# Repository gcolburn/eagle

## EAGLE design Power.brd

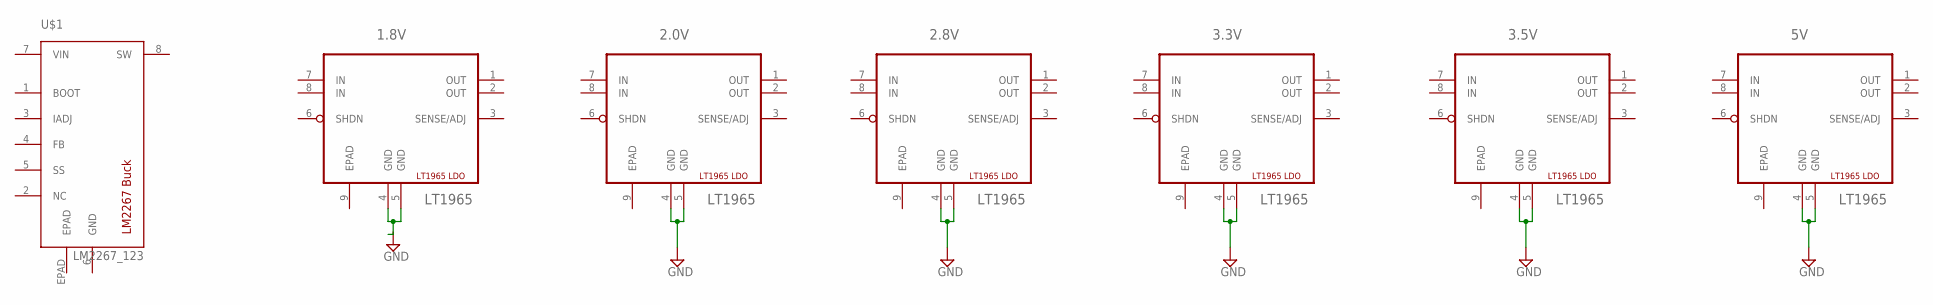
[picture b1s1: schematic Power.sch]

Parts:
1.8V, 2.0V, 2.8V, 3.3V, 3.5V, 5V: LT1965; DFN3X3_8LEAD
U$1: LM2267_123; DDA0008B

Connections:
BOOT: U$1.1 (BOOT)
EPAD: 1.8V.9 (EPAD), 2.0V.9 (EPAD), 2.8V.9 (EPAD), 3.3V.9 (EPAD), 3.5V.9 (EPAD), 5V.9 (EPAD), U$1.EPAD
GND: 2.0V.4 (GND), 2.0V.5 (GND), 2.8V.4 (GND), 2.8V.5 (GND), 3.3V.4 (GND), 3.3V.5 (GND), 3.5V.4 (GND), 3.5V.5 (GND), 5V.4 (GND), 5V.5 (GND), U$1.6 (GND)
IN: 1.8V.7 (IN), 1.8V.8 (IN), 2.0V.7 (IN), 2.0V.8 (IN), 2.8V.7 (IN), 2.8V.8 (IN), 3.3V.7 (IN), 3.3V.8 (IN), 3.5V.7 (IN), 3.5V.8 (IN), 5V.7 (IN), 5V.8 (IN)
unnamed: 1.8V.4 (GND), 1.8V.5 (GND)
OUT: 1.8V.1 (OUT), 1.8V.2 (OUT), 2.0V.1 (OUT), 2.0V.2 (OUT), 2.8V.1 (OUT), 2.8V.2 (OUT), 3.3V.1 (OUT), 3.3V.2 (OUT), 3.5V.1 (OUT), 3.5V.2 (OUT), 5V.1 (OUT), 5V.2 (OUT)
SW: U$1.8 (SW)
VIN: U$1.7 (VIN)

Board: 2 copper layers, 7 parts (0 on the bottom side), 5 nets, no tracks yet.

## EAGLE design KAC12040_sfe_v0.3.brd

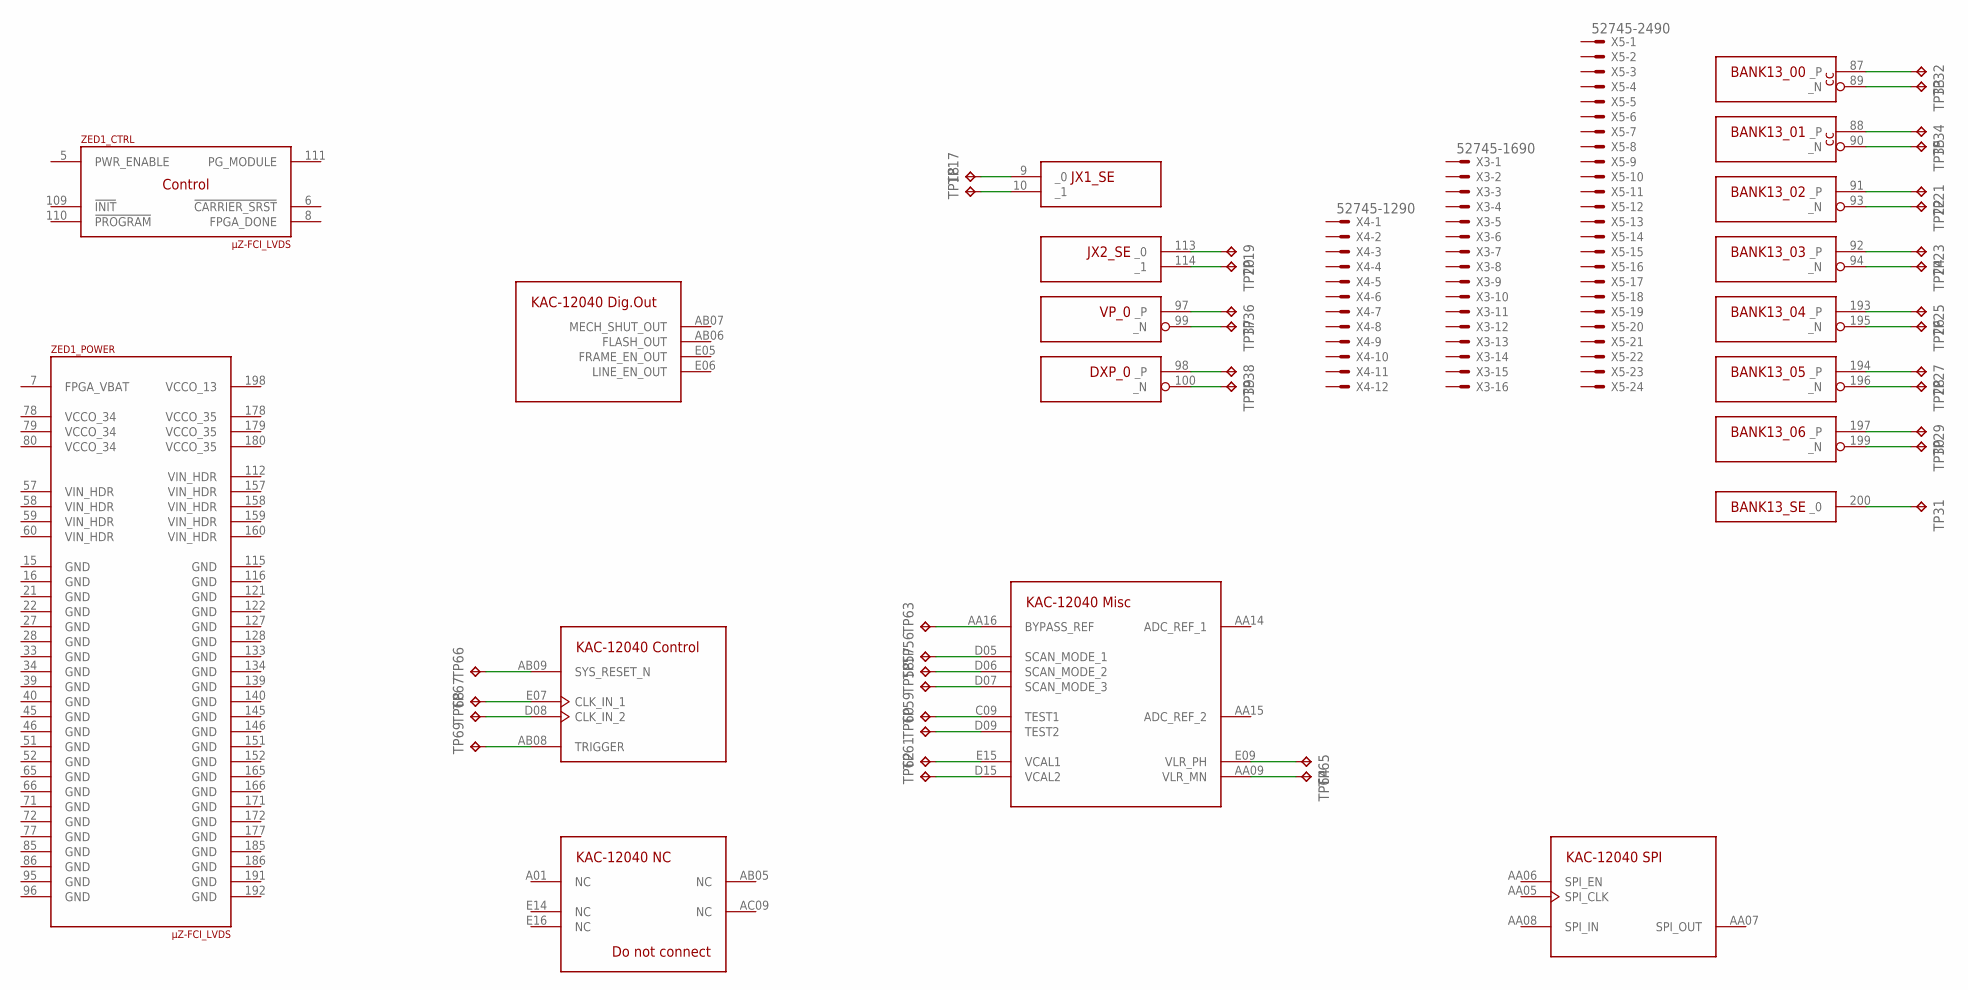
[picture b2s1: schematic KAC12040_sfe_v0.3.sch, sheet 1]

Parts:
TP17, TP18, TP19, TP20, TP31: TPPAD1-13; P1-13
TP21, TP22, TP23, TP24, TP25, TP26, TP27, TP28, TP29, TP30: TPTP08SQ; TP08SQ
TP32, TP33, TP34, TP35: TPTP18SQ; TP18SQ
TP36, TP37, TP38, TP39: TPPAD1-13Y; P1-13Y
TP56, TP57, TP58, TP59, TP60, TP61, TP62, TP63, TP64, TP65: TPTP15SQ; TP15SQ
TP66, TP67, TP68, TP69: TPTP15R; TP15R
U$1: KAC-12040-RB501T4
X3: 52745-1690
X4: 52745-1290
X5: 52745-2490
ZED1: µZ-FCI_LVDS; µZ

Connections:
FPGA_VBAT: ZED1.7 (FPGA_VBAT)
GND: ZED1.15 (GND), ZED1.16 (GND), ZED1.21 (GND), ZED1.22 (GND), ZED1.27 (GND), ZED1.28 (GND), ZED1.33 (GND), ZED1.34 (GND), ZED1.39 (GND), ZED1.40 (GND), ZED1.45 (GND), ZED1.46 (GND), ZED1.51 (GND), ZED1.52 (GND), ZED1.65 (GND), ZED1.66 (GND), ZED1.71 (GND), ZED1.72 (GND), ZED1.77 (GND), ZED1.85 (GND), ZED1.86 (GND), ZED1.95 (GND), ZED1.96 (GND), ZED1.115 (GND), ZED1.116 (GND), ZED1.121 (GND), ZED1.122 (GND), ZED1.127 (GND), ZED1.128 (GND), ZED1.133 (GND), ZED1.134 (GND), ZED1.139 (GND), ZED1.140 (GND), ZED1.145 (GND), ZED1.146 (GND), ZED1.151 (GND), ZED1.152 (GND), ZED1.165 (GND), ZED1.166 (GND), ZED1.171 (GND), ZED1.172 (GND), ZED1.177 (GND), ZED1.185 (GND), ZED1.186 (GND), ZED1.191 (GND), ZED1.192 (GND); also elsewhere on the board
unnamed: TP62.TP, U$1.D15 (VCAL2)
unnamed: TP61.TP, U$1.E15 (VCAL1)
unnamed: TP60.TP, U$1.D09 (TEST2)
unnamed: TP59.TP, U$1.C09 (TEST1)
unnamed: TP19.TP, ZED1.113 (_0)
unnamed: TP20.TP, ZED1.114 (_1)
unnamed: TP17.TP, ZED1.9 (_0)
unnamed: TP18.TP, ZED1.10 (_1)
unnamed: TP21.TP, ZED1.91 (_P)
unnamed: TP22.TP, ZED1.93 (_N)
unnamed: TP23.TP, ZED1.92 (_P)
unnamed: TP24.TP, ZED1.94 (_N)
unnamed: TP25.TP, ZED1.193 (_P)
unnamed: TP26.TP, ZED1.195 (_N)
unnamed: TP27.TP, ZED1.194 (_P)
unnamed: TP28.TP, ZED1.196 (_N)
unnamed: TP29.TP, ZED1.197 (_P)
unnamed: TP30.TP, ZED1.199 (_N)
unnamed: TP31.TP, ZED1.200 (_0)
unnamed: TP32.TP, ZED1.87 (_P)
unnamed: TP33.TP, ZED1.89 (_N)
unnamed: TP34.TP, ZED1.88 (_P)
unnamed: TP35.TP, ZED1.90 (_N)
unnamed: TP36.TP, ZED1.97 (_P)
unnamed: TP37.TP, ZED1.99 (_N)
unnamed: TP38.TP, ZED1.98 (_P)
unnamed: TP39.TP, ZED1.100 (_N)
unnamed: TP58.TP, U$1.D07 (SCAN_MODE_3)
unnamed: TP57.TP, U$1.D06 (SCAN_MODE_2)
unnamed: TP56.TP, U$1.D05 (SCAN_MODE_1)
unnamed: TP63.TP, U$1.AA16 (BYPASS_REF)
unnamed: TP65.TP, U$1.E09 (VLR_PH)
unnamed: TP64.TP, U$1.AA09 (VLR_MN)
unnamed: TP66.TP, U$1.AB09 (SYS_RESET_N)
unnamed: TP67.TP, U$1.E07 (CLK_IN_1)
unnamed: TP68.TP, U$1.D08 (CLK_IN_2)
unnamed: TP69.TP, U$1.AB08 (TRIGGER)
VCCO_13: ZED1.198 (VCCO_13)
VCCO_34: ZED1.78 (VCCO_34), ZED1.79 (VCCO_34), ZED1.80 (VCCO_34)
VCCO_35: ZED1.178 (VCCO_35), ZED1.179 (VCCO_35), ZED1.180 (VCCO_35)
VDDO: U$1.AB15 (VDDO)
VDD_PLL: U$1.E08 (VDD_PLL)
VIN_HDR: ZED1.57 (VIN_HDR), ZED1.58 (VIN_HDR), ZED1.59 (VIN_HDR), ZED1.60 (VIN_HDR), ZED1.112 (VIN_HDR), ZED1.157 (VIN_HDR), ZED1.158 (VIN_HDR), ZED1.159 (VIN_HDR), ZED1.160 (VIN_HDR)

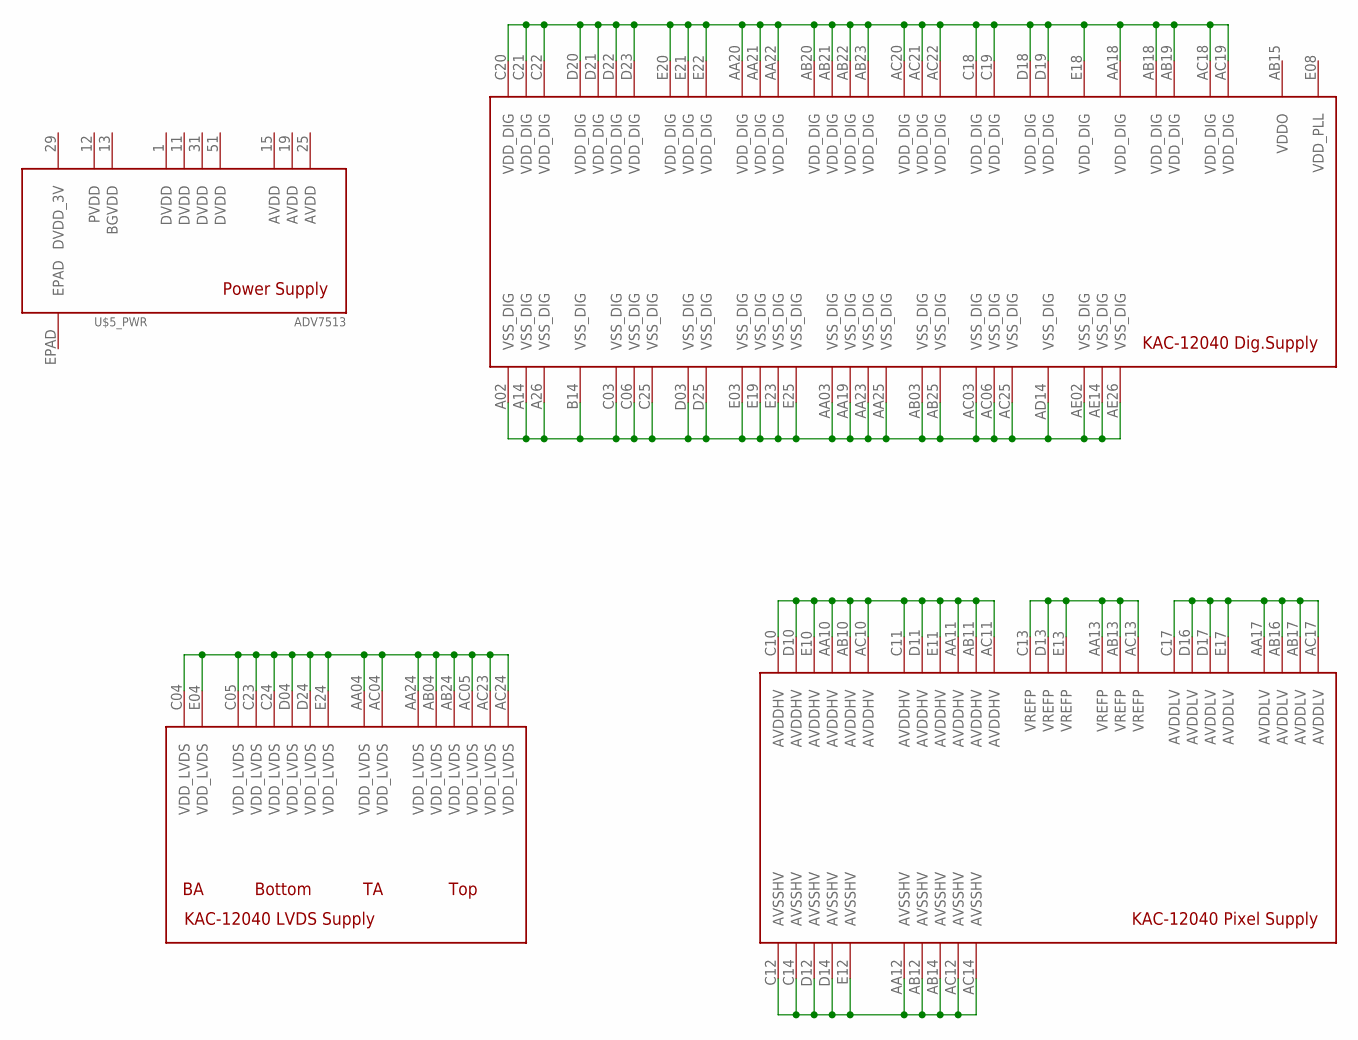
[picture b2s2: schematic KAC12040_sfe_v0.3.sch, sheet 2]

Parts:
U$1: KAC-12040-RB501T4
U$5: ADV7513; LQFP-ST-64-2

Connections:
AVDD: U$5.15 (AVDD), U$5.19 (AVDD), U$5.25 (AVDD)
AVDD_HV: U$1.AA10 (AVDDHV), U$1.AA11 (AVDDHV), U$1.AB10 (AVDDHV), U$1.AB11 (AVDDHV), U$1.AC10 (AVDDHV), U$1.AC11 (AVDDHV), U$1.C10 (AVDDHV), U$1.C11 (AVDDHV), U$1.D10 (AVDDHV), U$1.D11 (AVDDHV), U$1.E10 (AVDDHV), U$1.E11 (AVDDHV)
AVDD_LV: U$1.AA17 (AVDDLV), U$1.AB16 (AVDDLV), U$1.AB17 (AVDDLV), U$1.AC17 (AVDDLV), U$1.C17 (AVDDLV), U$1.D16 (AVDDLV), U$1.D17 (AVDDLV), U$1.E17 (AVDDLV)
AVSS_HV: U$1.AA12 (AVSSHV), U$1.AB12 (AVSSHV), U$1.AB14 (AVSSHV), U$1.AC12 (AVSSHV), U$1.AC14 (AVSSHV), U$1.C12 (AVSSHV), U$1.C14 (AVSSHV), U$1.D12 (AVSSHV), U$1.D14 (AVSSHV), U$1.E12 (AVSSHV)
BGVDD: U$5.13 (BGVDD)
DVDD: U$5.1 (DVDD), U$5.11 (DVDD), U$5.31 (DVDD), U$5.51 (DVDD)
DVDD_3V: U$5.29 (DVDD_3V)
EPAD: U$5.EPAD; also elsewhere on the board
PVDD: U$5.12 (PVDD)
VDDO: U$1.AB15 (VDDO)
VDD_DIG: U$1.AA18 (VDD_DIG), U$1.AA20 (VDD_DIG), U$1.AA21 (VDD_DIG), U$1.AA22 (VDD_DIG), U$1.AB18 (VDD_DIG), U$1.AB19 (VDD_DIG), U$1.AB20 (VDD_DIG), U$1.AB21 (VDD_DIG), U$1.AB22 (VDD_DIG), U$1.AB23 (VDD_DIG), U$1.AC18 (VDD_DIG), U$1.AC19 (VDD_DIG), U$1.AC20 (VDD_DIG), U$1.AC21 (VDD_DIG), U$1.AC22 (VDD_DIG), U$1.C18 (VDD_DIG), U$1.C19 (VDD_DIG), U$1.C20 (VDD_DIG), U$1.C21 (VDD_DIG), U$1.C22 (VDD_DIG), U$1.D18 (VDD_DIG), U$1.D19 (VDD_DIG), U$1.D20 (VDD_DIG), U$1.D21 (VDD_DIG), U$1.D22 (VDD_DIG), U$1.D23 (VDD_DIG), U$1.E18 (VDD_DIG), U$1.E20 (VDD_DIG), U$1.E21 (VDD_DIG), U$1.E22 (VDD_DIG)
VDD_LVDS: U$1.AA04 (VDD_LVDS), U$1.AA24 (VDD_LVDS), U$1.AB04 (VDD_LVDS), U$1.AB24 (VDD_LVDS), U$1.AC04 (VDD_LVDS), U$1.AC05 (VDD_LVDS), U$1.AC23 (VDD_LVDS), U$1.AC24 (VDD_LVDS), U$1.C04 (VDD_LVDS), U$1.C05 (VDD_LVDS), U$1.C23 (VDD_LVDS), U$1.C24 (VDD_LVDS), U$1.D04 (VDD_LVDS), U$1.D24 (VDD_LVDS), U$1.E04 (VDD_LVDS), U$1.E24 (VDD_LVDS)
VDD_PLL: U$1.E08 (VDD_PLL)
VREFP: U$1.AA13 (VREFP), U$1.AB13 (VREFP), U$1.AC13 (VREFP), U$1.C13 (VREFP), U$1.D13 (VREFP), U$1.E13 (VREFP)
VSS_DIG: U$1.A02 (VSS_DIG), U$1.A14 (VSS_DIG), U$1.A26 (VSS_DIG), U$1.AA03 (VSS_DIG), U$1.AA19 (VSS_DIG), U$1.AA23 (VSS_DIG), U$1.AA25 (VSS_DIG), U$1.AB03 (VSS_DIG), U$1.AB25 (VSS_DIG), U$1.AC03 (VSS_DIG), U$1.AC06 (VSS_DIG), U$1.AC25 (VSS_DIG), U$1.AD14 (VSS_DIG), U$1.AE02 (VSS_DIG), U$1.AE14 (VSS_DIG), U$1.AE26 (VSS_DIG), U$1.B14 (VSS_DIG), U$1.C03 (VSS_DIG), U$1.C06 (VSS_DIG), U$1.C25 (VSS_DIG), U$1.D03 (VSS_DIG), U$1.D25 (VSS_DIG), U$1.E03 (VSS_DIG), U$1.E19 (VSS_DIG), U$1.E23 (VSS_DIG), U$1.E25 (VSS_DIG)

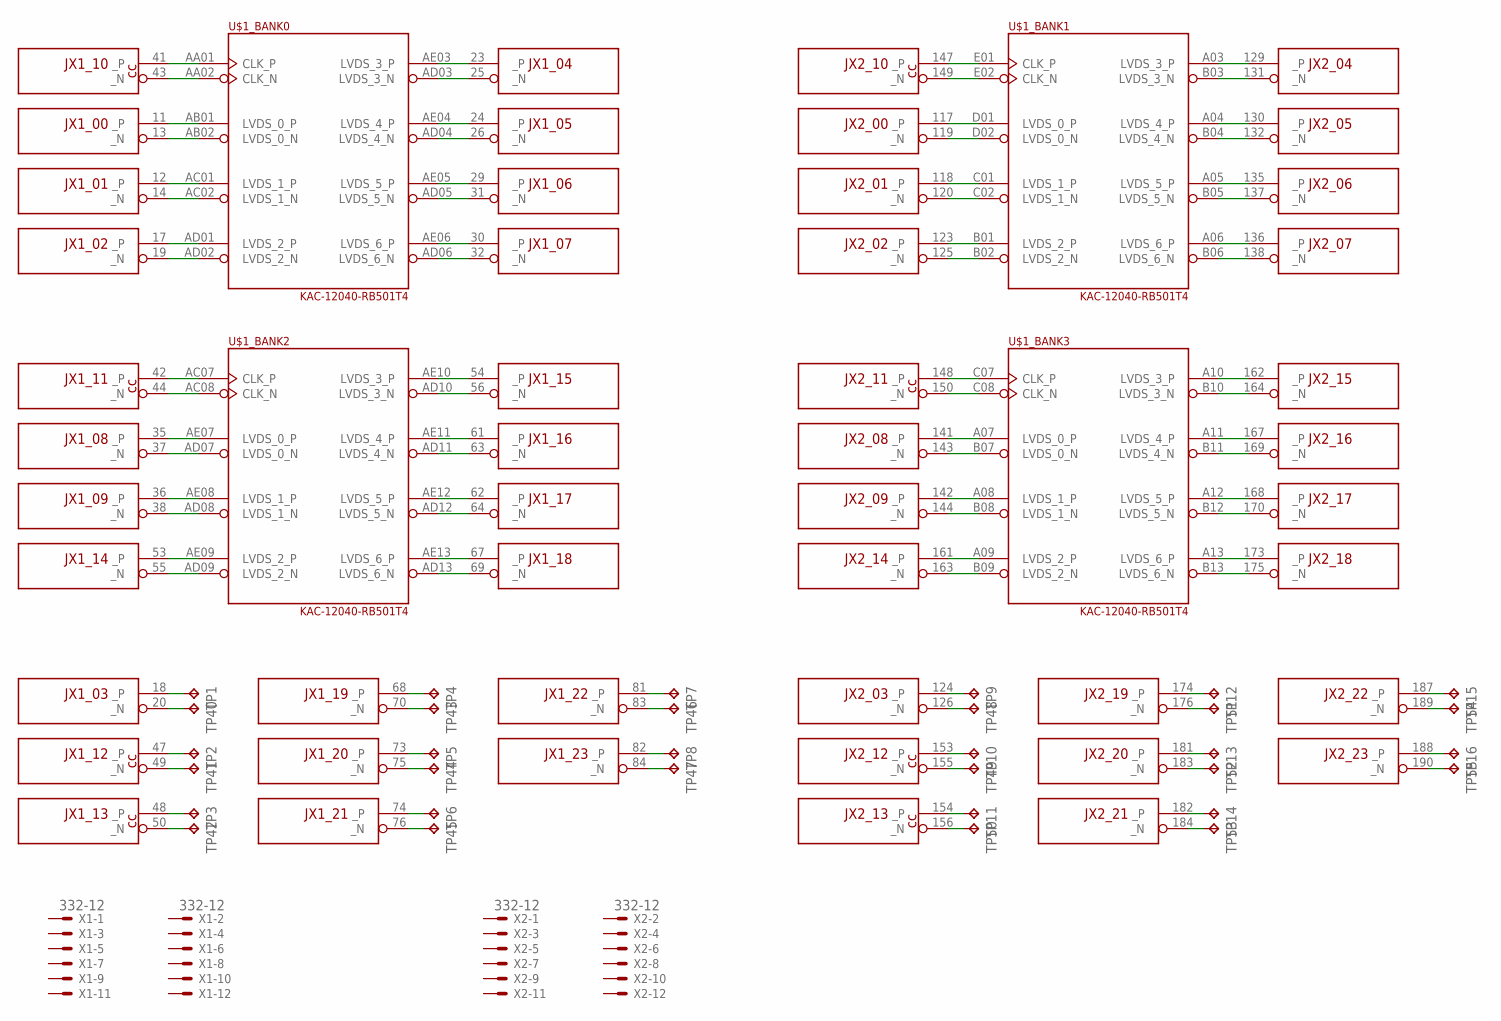
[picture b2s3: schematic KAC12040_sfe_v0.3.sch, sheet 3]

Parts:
TP1, TP4, TP5, TP6, TP7, TP8, TP9, TP12, TP13, TP14, TP15, TP16, TP40, TP43, TP44, TP45, TP46, TP47, TP48, TP51, TP52, TP53, TP54, TP55: TPTP10R; TP10R
TP2, TP3, TP10, TP11, TP41, TP42, TP49, TP50: TPTP20R; TP20R
U$1: KAC-12040-RB501T4
X1, X2: 332-12
ZED1: µZ-FCI_LVDS; µZ

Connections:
C$0_N: U$1.AA02 (CLK_N), ZED1.43 (_N)
C$0_P: U$1.AA01 (CLK_P), ZED1.41 (_P)
C$1_N: U$1.E02 (CLK_N), ZED1.149 (_N)
C$1_P: U$1.E01 (CLK_P), ZED1.147 (_P)
C$2_N: U$1.AC08 (CLK_N), ZED1.44 (_N)
C$2_P: U$1.AC07 (CLK_P), ZED1.42 (_P)
C$3_N: U$1.C08 (CLK_N), ZED1.150 (_N)
C$3_P: U$1.C07 (CLK_P), ZED1.148 (_P)
FPGA_VBAT: ZED1.7 (FPGA_VBAT)
GND: ZED1.15 (GND), ZED1.16 (GND), ZED1.21 (GND), ZED1.22 (GND), ZED1.27 (GND), ZED1.28 (GND), ZED1.33 (GND), ZED1.34 (GND), ZED1.39 (GND), ZED1.40 (GND), ZED1.45 (GND), ZED1.46 (GND), ZED1.51 (GND), ZED1.52 (GND), ZED1.65 (GND), ZED1.66 (GND), ZED1.71 (GND), ZED1.72 (GND), ZED1.77 (GND), ZED1.85 (GND), ZED1.86 (GND), ZED1.95 (GND), ZED1.96 (GND), ZED1.115 (GND), ZED1.116 (GND), ZED1.121 (GND), ZED1.122 (GND), ZED1.127 (GND), ZED1.128 (GND), ZED1.133 (GND), ZED1.134 (GND), ZED1.139 (GND), ZED1.140 (GND), ZED1.145 (GND), ZED1.146 (GND), ZED1.151 (GND), ZED1.152 (GND), ZED1.165 (GND), ZED1.166 (GND), ZED1.171 (GND), ZED1.172 (GND), ZED1.177 (GND), ZED1.185 (GND), ZED1.186 (GND), ZED1.191 (GND), ZED1.192 (GND); also elsewhere on the board
L0$0_N: U$1.AB02 (LVDS_0_N), ZED1.13 (_N)
L0$0_P: U$1.AB01 (LVDS_0_P), ZED1.11 (_P)
L0$1_N: U$1.D02 (LVDS_0_N), ZED1.119 (_N)
L0$1_P: U$1.D01 (LVDS_0_P), ZED1.117 (_P)
L0$2_N: U$1.AD07 (LVDS_0_N), ZED1.37 (_N)
L0$2_P: U$1.AE07 (LVDS_0_P), ZED1.35 (_P)
L0$3_N: U$1.B07 (LVDS_0_N), ZED1.143 (_N)
L0$3_P: U$1.A07 (LVDS_0_P), ZED1.141 (_P)
L1$0_N: U$1.AC02 (LVDS_1_N), ZED1.14 (_N)
L1$0_P: U$1.AC01 (LVDS_1_P), ZED1.12 (_P)
L1$1_N: U$1.C02 (LVDS_1_N), ZED1.120 (_N)
L1$1_P: U$1.C01 (LVDS_1_P), ZED1.118 (_P)
L1$2_N: U$1.AD08 (LVDS_1_N), ZED1.38 (_N)
L1$2_P: U$1.AE08 (LVDS_1_P), ZED1.36 (_P)
L1$3_N: U$1.B08 (LVDS_1_N), ZED1.144 (_N)
L1$3_P: U$1.A08 (LVDS_1_P), ZED1.142 (_P)
L2$0_N: U$1.AD02 (LVDS_2_N), ZED1.19 (_N)
L2$0_P: U$1.AD01 (LVDS_2_P), ZED1.17 (_P)
L2$1_N: U$1.B02 (LVDS_2_N), ZED1.125 (_N)
L2$1_P: U$1.B01 (LVDS_2_P), ZED1.123 (_P)
L2$2_N: U$1.AD09 (LVDS_2_N), ZED1.55 (_N)
L2$2_P: U$1.AE09 (LVDS_2_P), ZED1.53 (_P)
L2$3_N: U$1.B09 (LVDS_2_N), ZED1.163 (_N)
L2$3_P: U$1.A09 (LVDS_2_P), ZED1.161 (_P)
L3$0_N: U$1.AD03 (LVDS_3_N), ZED1.25 (_N)
L3$0_P: U$1.AE03 (LVDS_3_P), ZED1.23 (_P)
L3$1_N: U$1.B03 (LVDS_3_N), ZED1.131 (_N)
L3$1_P: U$1.A03 (LVDS_3_P), ZED1.129 (_P)
L3$2_N: U$1.AD10 (LVDS_3_N), ZED1.56 (_N)
L3$2_P: U$1.AE10 (LVDS_3_P), ZED1.54 (_P)
L3$3_N: U$1.B10 (LVDS_3_N), ZED1.164 (_N)
L3$3_P: U$1.A10 (LVDS_3_P), ZED1.162 (_P)
L4$0_N: U$1.AD04 (LVDS_4_N), ZED1.26 (_N)
L4$0_P: U$1.AE04 (LVDS_4_P), ZED1.24 (_P)
L4$1_N: U$1.B04 (LVDS_4_N), ZED1.132 (_N)
L4$1_P: U$1.A04 (LVDS_4_P), ZED1.130 (_P)
L4$2_N: U$1.AD11 (LVDS_4_N), ZED1.63 (_N)
L4$2_P: U$1.AE11 (LVDS_4_P), ZED1.61 (_P)
L4$3_N: U$1.B11 (LVDS_4_N), ZED1.169 (_N)
L4$3_P: U$1.A11 (LVDS_4_P), ZED1.167 (_P)
L5$0_N: U$1.AD05 (LVDS_5_N), ZED1.31 (_N)
L5$0_P: U$1.AE05 (LVDS_5_P), ZED1.29 (_P)
L5$1_N: U$1.B05 (LVDS_5_N), ZED1.137 (_N)
L5$1_P: U$1.A05 (LVDS_5_P), ZED1.135 (_P)
L5$2_N: U$1.AD12 (LVDS_5_N), ZED1.64 (_N)
L5$2_P: U$1.AE12 (LVDS_5_P), ZED1.62 (_P)
L5$3_N: U$1.B12 (LVDS_5_N), ZED1.170 (_N)
L5$3_P: U$1.A12 (LVDS_5_P), ZED1.168 (_P)
L6$0_N: U$1.AD06 (LVDS_6_N), ZED1.32 (_N)
L6$0_P: U$1.AE06 (LVDS_6_P), ZED1.30 (_P)
L6$1_N: U$1.B06 (LVDS_6_N), ZED1.138 (_N)
L6$1_P: U$1.A06 (LVDS_6_P), ZED1.136 (_P)
L6$2_N: U$1.AD13 (LVDS_6_N), ZED1.69 (_N)
L6$2_P: U$1.AE13 (LVDS_6_P), ZED1.67 (_P)
L6$3_N: U$1.B13 (LVDS_6_N), ZED1.175 (_N)
L6$3_P: U$1.A13 (LVDS_6_P), ZED1.173 (_P)
unnamed: TP15.TP, ZED1.187 (_P)
unnamed: TP12.TP, ZED1.174 (_P)
unnamed: TP9.TP, ZED1.124 (_P)
unnamed: TP7.TP, ZED1.81 (_P)
unnamed: TP4.TP, ZED1.68 (_P)
unnamed: TP1.TP, ZED1.18 (_P)
unnamed: TP2.TP, ZED1.47 (_P)
unnamed: TP3.TP, ZED1.48 (_P)
unnamed: TP5.TP, ZED1.73 (_P)
unnamed: TP6.TP, ZED1.74 (_P)
unnamed: TP8.TP, ZED1.82 (_P)
unnamed: TP10.TP, ZED1.153 (_P)
unnamed: TP11.TP, ZED1.154 (_P)
unnamed: TP13.TP, ZED1.181 (_P)
unnamed: TP14.TP, ZED1.182 (_P)
unnamed: TP16.TP, ZED1.188 (_P)
unnamed: TP40.TP, ZED1.20 (_N)
unnamed: TP41.TP, ZED1.49 (_N)
unnamed: TP42.TP, ZED1.50 (_N)
unnamed: TP43.TP, ZED1.70 (_N)
unnamed: TP44.TP, ZED1.75 (_N)
unnamed: TP45.TP, ZED1.76 (_N)
unnamed: TP46.TP, ZED1.83 (_N)
unnamed: TP47.TP, ZED1.84 (_N)
unnamed: TP48.TP, ZED1.126 (_N)
unnamed: TP49.TP, ZED1.155 (_N)
unnamed: TP50.TP, ZED1.156 (_N)
unnamed: TP51.TP, ZED1.176 (_N)
unnamed: TP52.TP, ZED1.183 (_N)
unnamed: TP53.TP, ZED1.184 (_N)
unnamed: TP54.TP, ZED1.189 (_N)
unnamed: TP55.TP, ZED1.190 (_N)
VCCO_13: ZED1.198 (VCCO_13)
VCCO_34: ZED1.78 (VCCO_34), ZED1.79 (VCCO_34), ZED1.80 (VCCO_34)
VCCO_35: ZED1.178 (VCCO_35), ZED1.179 (VCCO_35), ZED1.180 (VCCO_35)
VDDO: U$1.AB15 (VDDO)
VDD_PLL: U$1.E08 (VDD_PLL)
VIN_HDR: ZED1.57 (VIN_HDR), ZED1.58 (VIN_HDR), ZED1.59 (VIN_HDR), ZED1.60 (VIN_HDR), ZED1.112 (VIN_HDR), ZED1.157 (VIN_HDR), ZED1.158 (VIN_HDR), ZED1.159 (VIN_HDR), ZED1.160 (VIN_HDR)

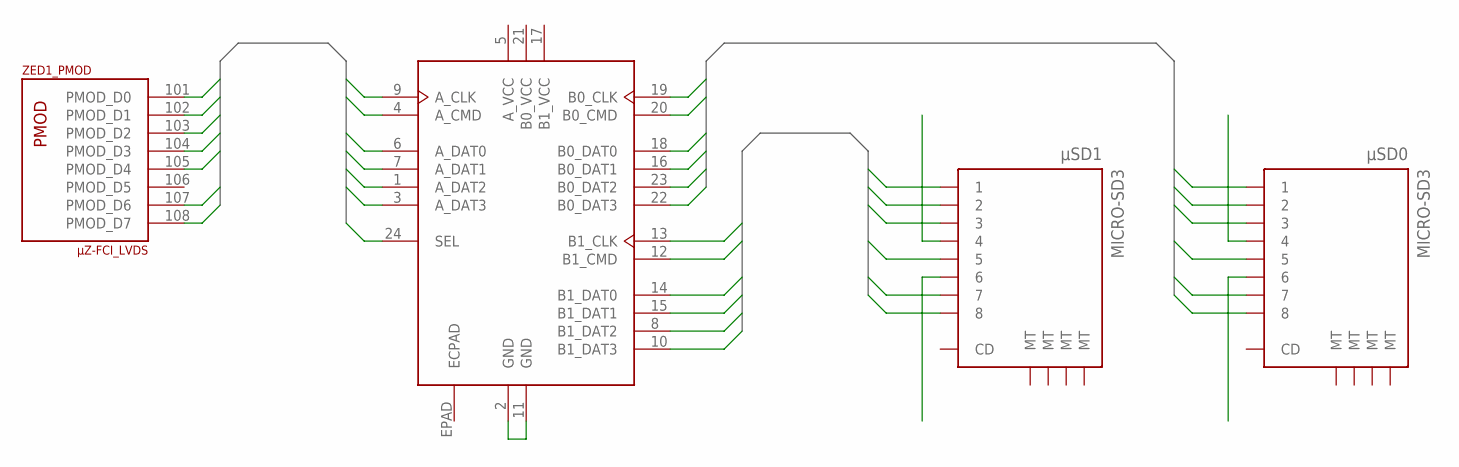
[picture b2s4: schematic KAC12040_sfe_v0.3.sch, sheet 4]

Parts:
U$4: TXS02612; S-PWQFN-N24
ZED1: µZ-FCI_LVDS; µZ
µSD0, µSD1: MICRO-SD3; TF-MICRO-SD_PP3

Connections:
A_CLK: U$4.9 (A_CLK), ZED1.104 (PMOD_D3)
A_CMD: U$4.4 (A_CMD), ZED1.103 (PMOD_D2)
A_DAT0: U$4.6 (A_DAT0), ZED1.102 (PMOD_D1)
A_DAT1: U$4.7 (A_DAT1), ZED1.101 (PMOD_D0)
A_DAT2: U$4.1 (A_DAT2), ZED1.107 (PMOD_D6)
A_DAT3: U$4.3 (A_DAT3), ZED1.108 (PMOD_D7)
A_VCC: U$4.5 (A_VCC)
B0_CLK: U$4.19 (B0_CLK), µSD0.5
B0_CMD: U$4.20 (B0_CMD), µSD0.3
B0_DAT0: U$4.18 (B0_DAT0), µSD0.7
B0_DAT1: U$4.16 (B0_DAT1), µSD0.8
B0_DAT2: U$4.23 (B0_DAT2), µSD0.1
B0_DAT3: U$4.22 (B0_DAT3), µSD0.2
B0_VCC: U$4.21 (B0_VCC)
B1_CLK: U$4.13 (B1_CLK), µSD1.5
B1_CMD: U$4.12 (B1_CMD), µSD1.3
B1_DAT0: U$4.14 (B1_DAT0), µSD1.7
B1_DAT1: U$4.15 (B1_DAT1), µSD1.8
B1_DAT2: U$4.8 (B1_DAT2), µSD1.1
B1_DAT3: U$4.10 (B1_DAT3), µSD1.2
B1_VCC: U$4.17 (B1_VCC)
ECPAD: U$4.EPAD (ECPAD)
FPGA_VBAT: ZED1.7 (FPGA_VBAT)
GND: ZED1.15 (GND), ZED1.16 (GND), ZED1.21 (GND), ZED1.22 (GND), ZED1.27 (GND), ZED1.28 (GND), ZED1.33 (GND), ZED1.34 (GND), ZED1.39 (GND), ZED1.40 (GND), ZED1.45 (GND), ZED1.46 (GND), ZED1.51 (GND), ZED1.52 (GND), ZED1.65 (GND), ZED1.66 (GND), ZED1.71 (GND), ZED1.72 (GND), ZED1.77 (GND), ZED1.85 (GND), ZED1.86 (GND), ZED1.95 (GND), ZED1.96 (GND), ZED1.115 (GND), ZED1.116 (GND), ZED1.121 (GND), ZED1.122 (GND), ZED1.127 (GND), ZED1.128 (GND), ZED1.133 (GND), ZED1.134 (GND), ZED1.139 (GND), ZED1.140 (GND), ZED1.145 (GND), ZED1.146 (GND), ZED1.151 (GND), ZED1.152 (GND), ZED1.165 (GND), ZED1.166 (GND), ZED1.171 (GND), ZED1.172 (GND), ZED1.177 (GND), ZED1.185 (GND), ZED1.186 (GND), ZED1.191 (GND), ZED1.192 (GND); also elsewhere on the board
MT: µSD0.MT1 (MT), µSD0.MT2 (MT), µSD0.MT3 (MT), µSD0.MT4 (MT), µSD1.MT1 (MT), µSD1.MT2 (MT), µSD1.MT3 (MT), µSD1.MT4 (MT)
unnamed: U$4.2 (GND), U$4.11 (GND)
SEL: U$4.24 (SEL), ZED1.105 (PMOD_D4)
VCCO_13: ZED1.198 (VCCO_13)
VCCO_34: ZED1.78 (VCCO_34), ZED1.79 (VCCO_34), ZED1.80 (VCCO_34)
VCCO_35: ZED1.178 (VCCO_35), ZED1.179 (VCCO_35), ZED1.180 (VCCO_35)
VIN_HDR: ZED1.57 (VIN_HDR), ZED1.58 (VIN_HDR), ZED1.59 (VIN_HDR), ZED1.60 (VIN_HDR), ZED1.112 (VIN_HDR), ZED1.157 (VIN_HDR), ZED1.158 (VIN_HDR), ZED1.159 (VIN_HDR), ZED1.160 (VIN_HDR)

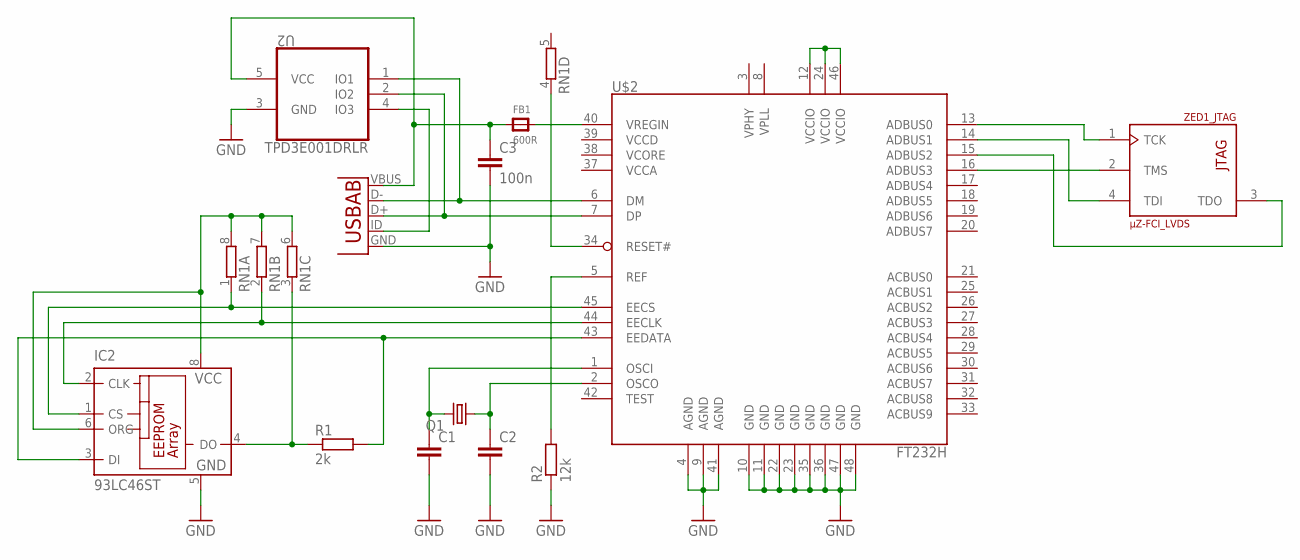
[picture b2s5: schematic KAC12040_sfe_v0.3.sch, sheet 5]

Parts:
C1, C2: C-EUC0402K; C0402K
C3: 100n; C0402K
FB1: 600R; _0603MP
IC2: 93LC46ST; TSSOP8
Q1: CRYSTALCTS406; CTS406
R1: 2k; R0402
R2: 12k; R0402
RN1: 4R-N0402ARV341; 4X0402ARV341
U1: USB-AB; USB-AB-MICRO-SMD
U2: TPD3E001DRLR; SOT50P160X60-5N
U$2: FT232H; LQFP48
ZED1: µZ-FCI_LVDS; µZ

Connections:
EE_CLK: IC2.2 (CLK), RN1.2 (1), U$2.44 (EECLK)
EE_CS: IC2.1 (CS), RN1.1, U$2.45 (EECS)
EE_DATA: IC2.3 (DI), R1.2, U$2.43 (EEDATA)
FPGA_VBAT: ZED1.7 (FPGA_VBAT)
GND: C1.2, C2.2, C3.2, IC2.5 (GND), R2.1, U1.GND, U2.3 (GND), U$2.4 (AGND), U$2.9 (AGND), U$2.10 (GND), U$2.11 (GND), U$2.22 (GND), U$2.23 (GND), U$2.35 (GND), U$2.36 (GND), U$2.41 (AGND), U$2.47 (GND), U$2.48 (GND), ZED1.15 (GND), ZED1.16 (GND), ZED1.21 (GND), ZED1.22 (GND), ZED1.27 (GND), ZED1.28 (GND), ZED1.33 (GND), ZED1.34 (GND), ZED1.39 (GND), ZED1.40 (GND), ZED1.45 (GND), ZED1.46 (GND), ZED1.51 (GND), ZED1.52 (GND), ZED1.65 (GND), ZED1.66 (GND), ZED1.71 (GND), ZED1.72 (GND), ZED1.77 (GND), ZED1.85 (GND), ZED1.86 (GND), ZED1.95 (GND), ZED1.96 (GND), ZED1.115 (GND), ZED1.116 (GND), ZED1.121 (GND), ZED1.122 (GND), ZED1.127 (GND), ZED1.128 (GND), ZED1.133 (GND), ZED1.134 (GND), ZED1.139 (GND), ZED1.140 (GND), ZED1.145 (GND), ZED1.146 (GND), ZED1.151 (GND), ZED1.152 (GND), ZED1.165 (GND), ZED1.166 (GND), ZED1.171 (GND), ZED1.172 (GND), ZED1.177 (GND), ZED1.185 (GND), ZED1.186 (GND), ZED1.191 (GND), ZED1.192 (GND); also elsewhere on the board
unnamed: FB1.2, U$2.40 (VREGIN)
unnamed: C3.1, FB1.1, U1.VBUS, U2.5 (VCC)
unnamed: IC2.4 (DO), R1.1, RN1.3 (1)
unnamed: IC2.6 (ORG), IC2.8 (VCC), RN1.6 (2), RN1.7 (2), RN1.8 (2)
unnamed: U$2.13 (ADBUS0), ZED1.1 (TCK)
unnamed: C1.1, Q1.3 (2), U$2.1 (OSCI)
unnamed: C2.1, Q1.1, U$2.2 (OSCO)
unnamed: U$2.14 (ADBUS1), ZED1.4 (TDI)
unnamed: U$2.15 (ADBUS2), ZED1.3 (TDO)
unnamed: U$2.16 (ADBUS3), ZED1.2 (TMS)
unnamed: U$2.12 (VCCIO), U$2.24 (VCCIO), U$2.46 (VCCIO)
unnamed: U1.ID (USBID), U2.4 (IO3)
unnamed: RN1.4 (1), U$2.34 (RESET#)
unnamed: U1.D+, U2.2 (IO2), U$2.7 (DP)
unnamed: U1.D-, U2.1 (IO1), U$2.6 (DM)
unnamed: R2.2, U$2.5 (REF)
VCCD: U$2.39 (VCCD)
VCCO_13: ZED1.198 (VCCO_13)
VCCO_34: ZED1.78 (VCCO_34), ZED1.79 (VCCO_34), ZED1.80 (VCCO_34)
VCCO_35: ZED1.178 (VCCO_35), ZED1.179 (VCCO_35), ZED1.180 (VCCO_35)
VIN_HDR: ZED1.57 (VIN_HDR), ZED1.58 (VIN_HDR), ZED1.59 (VIN_HDR), ZED1.60 (VIN_HDR), ZED1.112 (VIN_HDR), ZED1.157 (VIN_HDR), ZED1.158 (VIN_HDR), ZED1.159 (VIN_HDR), ZED1.160 (VIN_HDR)
VPHY: U$2.3 (VPHY)
VPLL: U$2.8 (VPLL)

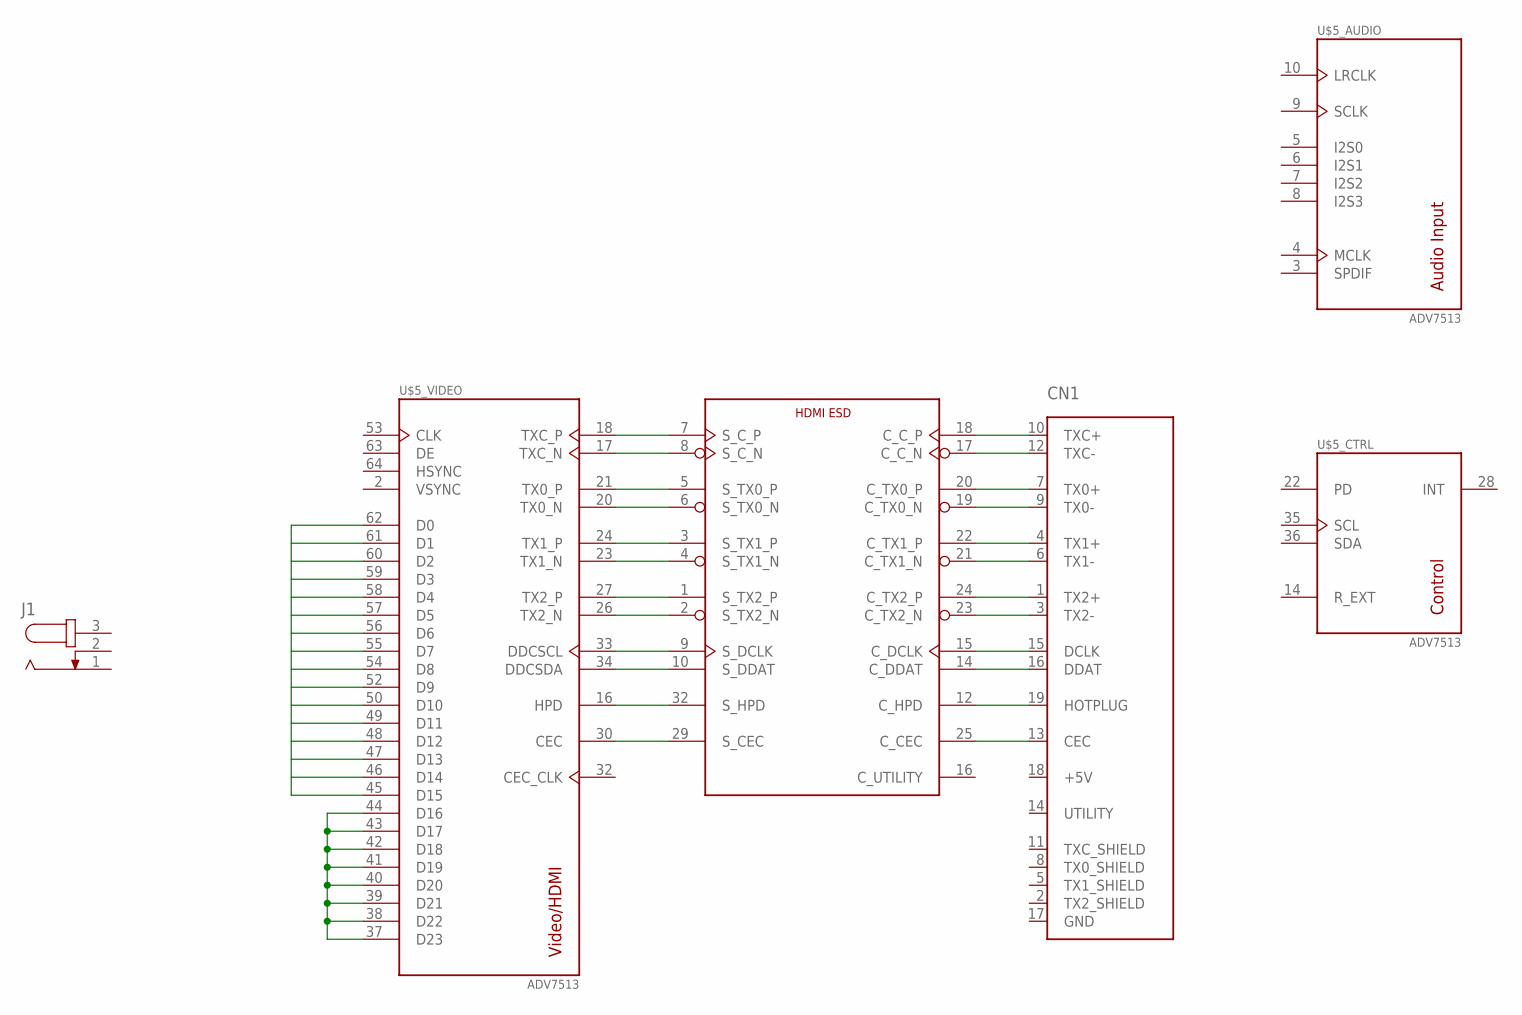
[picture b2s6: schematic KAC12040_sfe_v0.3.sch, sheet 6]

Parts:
CN1: HDMI_MOLEX_47151-0001
J1: JACK-PLUG0; SPC4077
U$3: IP4786CZ32SOT617-3; SOT617-3
U$5: ADV7513; LQFP-ST-64-2

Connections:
+5V: CN1.18 (+5V)
AVDD: U$5.15 (AVDD), U$5.19 (AVDD), U$5.25 (AVDD)
BGVDD: U$5.13 (BGVDD)
C_5V: U$3.13 (C_5V)
DVDD: U$5.1 (DVDD), U$5.11 (DVDD), U$5.31 (DVDD), U$5.51 (DVDD)
DVDD_3V: U$5.29 (DVDD_3V)
EPAD: U$3.EPAD, U$5.EPAD
GND: CN1.17 (GND), CN1.P$1 (GND), CN1.P$2 (GND), CN1.P$3 (GND), CN1.P$4 (GND); also elsewhere on the board
unnamed: U$3.7 (S_C_P), U$5.18 (TXC_P)
unnamed: U$3.8 (S_C_N), U$5.17 (TXC_N)
unnamed: U$3.5 (S_TX0_P), U$5.21 (TX0_P)
unnamed: U$3.6 (S_TX0_N), U$5.20 (TX0_N)
unnamed: U$3.3 (S_TX1_P), U$5.24 (TX1_P)
unnamed: U$3.4 (S_TX1_N), U$5.23 (TX1_N)
unnamed: U$3.1 (S_TX2_P), U$5.27 (TX2_P)
unnamed: U$3.2 (S_TX2_N), U$5.26 (TX2_N)
unnamed: U$3.9 (S_DCLK), U$5.33 (DDCSCL)
unnamed: U$3.10 (S_DDAT), U$5.34 (DDCSDA)
unnamed: U$3.32 (S_HPD), U$5.16 (HPD)
unnamed: U$3.29 (S_CEC), U$5.30 (CEC)
unnamed: CN1.13 (CEC), U$3.25 (C_CEC)
unnamed: CN1.19 (HOTPLUG), U$3.12 (C_HPD)
unnamed: CN1.16 (DDAT), U$3.14 (C_DDAT)
unnamed: CN1.15 (DCLK), U$3.15 (C_DCLK)
unnamed: CN1.3 (TX2-), U$3.23 (C_TX2_N)
unnamed: CN1.1 (TX2+), U$3.24 (C_TX2_P)
unnamed: CN1.6 (TX1-), U$3.21 (C_TX1_N)
unnamed: CN1.4 (TX1+), U$3.22 (C_TX1_P)
unnamed: CN1.9 (TX0-), U$3.19 (C_TX0_N)
unnamed: CN1.7 (TX0+), U$3.20 (C_TX0_P)
unnamed: CN1.12 (TXC-), U$3.17 (C_C_N)
unnamed: CN1.10 (TXC+), U$3.18 (C_C_P)
unnamed: U$5.45 (D15), U$5.46 (D14), U$5.47 (D13), U$5.48 (D12), U$5.49 (D11), U$5.50 (D10), U$5.52 (D9), U$5.54 (D8), U$5.55 (D7), U$5.56 (D6), U$5.57 (D5), U$5.58 (D4), U$5.59 (D3), U$5.60 (D2), U$5.61 (D1), U$5.62 (D0)
unnamed: U$5.37 (D23), U$5.38 (D22), U$5.39 (D21), U$5.40 (D20), U$5.41 (D19), U$5.42 (D18), U$5.43 (D17), U$5.44 (D16)
PVDD: U$5.12 (PVDD)
S_VCC: U$3.27 (S_VCC)
TX0_SHIELD: CN1.8 (TX0_SHIELD)
TX1_SHIELD: CN1.5 (TX1_SHIELD)
TX2_SHIELD: CN1.2 (TX2_SHIELD)
TXC_SHIELD: CN1.11 (TXC_SHIELD)
VCC5V: U$3.11 (VCC5V)

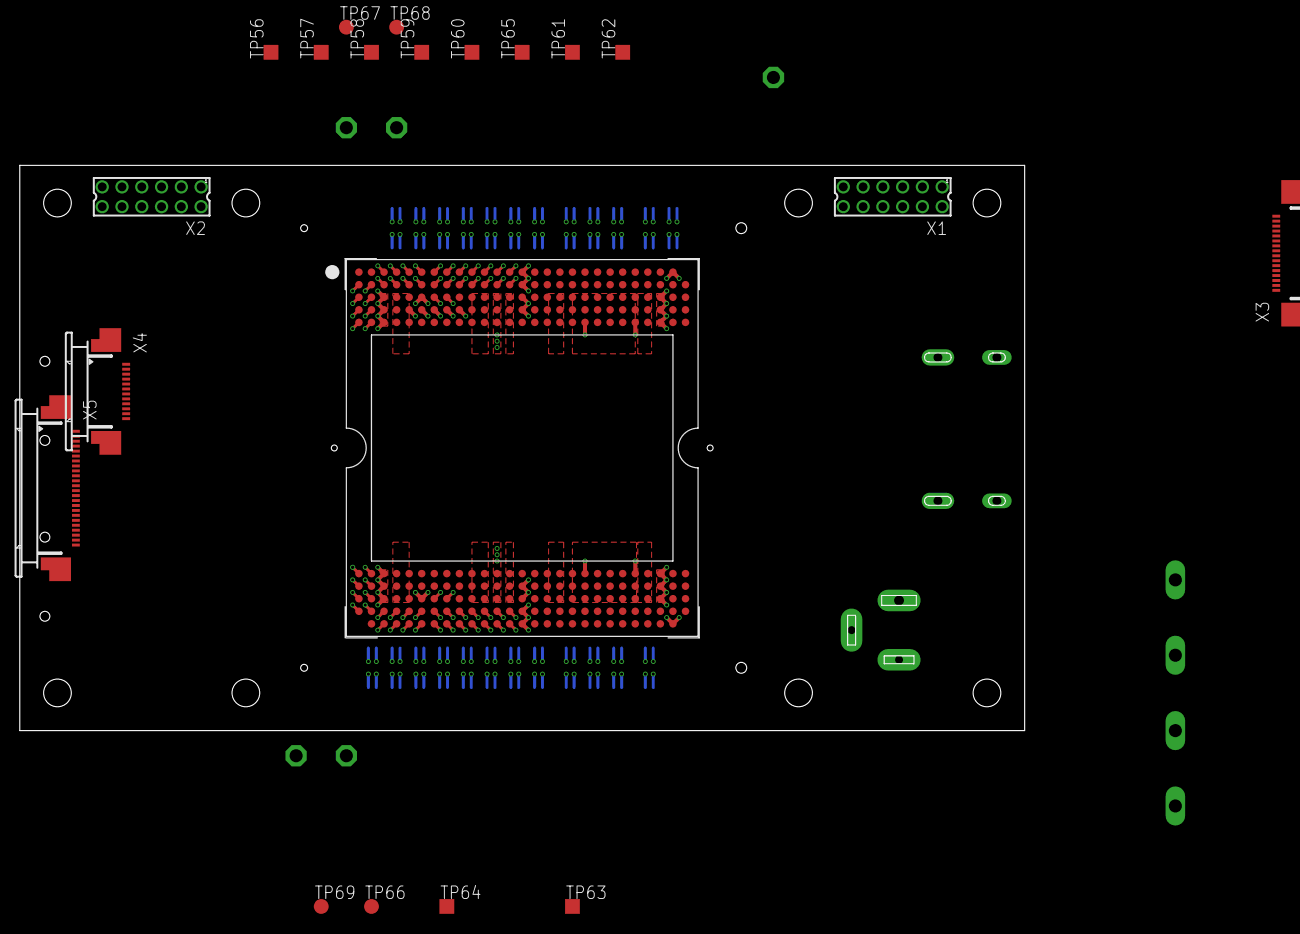
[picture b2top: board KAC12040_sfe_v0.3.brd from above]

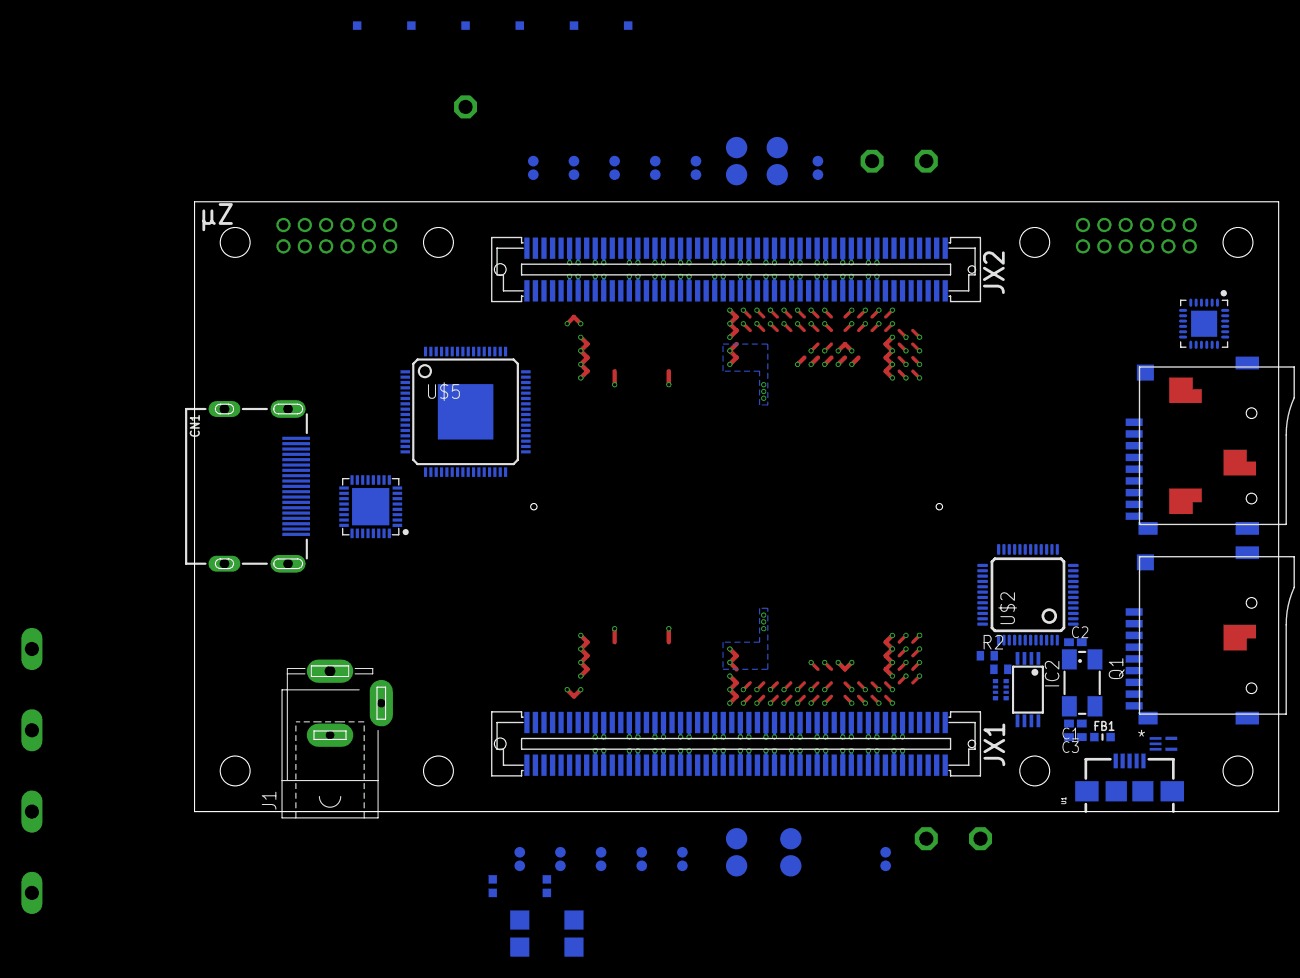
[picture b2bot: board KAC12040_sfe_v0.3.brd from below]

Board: 4 copper layers, 101.6 x 57.1 mm, 95 parts (66 on the bottom side), 213 nets.

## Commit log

2014-01-11 Fixed silkscreen
2014-01-15 Added schematic
2014-01-15 Updated schematic
2014-01-16 Added device
2014-01-16 Added thermal pad
2014-01-21 Added Andon socket outer dimension and pads
2014-01-21 Added side radii
2014-01-23 Added KAC LVDS Bank Schematic
2014-01-27 Added KAC CTL Schematic
2014-01-27 Added power and bias schematics
2014-01-28 Added NC pins
2014-01-28 Added sensor dimensions to footprint
2014-01-29 Added KAC-12040 part
2014-01-30 just a test
2014-01-30 Updated Eagle Libraries
    - moved TXS02612 into separate library
    - added micro-sd.lbr
    - added microzed.lbr
    - cleanup for KAC-12040.lbr
2014-01-30 Some Library Adjustments
    - Consistent XYY and XXYY labeling
    - Extension via underscore
    - Spacing for Banks
2014-01-30 Initial take on the LVDS connections
2014-01-30 Differential net names for LVDS
2014-01-30 Mockup with unconnected parts
2014-01-30 Added SM sensor socket package
2014-01-30 Added SM pad script for sensor package
2014-01-31 Minor updates to existing Libraries
    - Connected the KAC SMT socket
    - Adjusted the TXS02612 schematic symbol
2014-01-31 Added the ADV7513 Library
2014-01-31 Minor library changes and part placement
2014-01-31 Another update to the design
    - Replaced FT2232H with FT232H (single channel)
    - Added SD PMOD interface
2014-02-01 Initial IP4786CZ32 HDMI ESD part
2014-02-01 Added EPAD to IP786CZ32
2014-02-02 Initial sensor route planning
2014-02-02 Basic power planes and vias
2014-02-02 Some minor updates
2014-02-08 Added LT1965 LDO Part
2014-02-08 Update to LT1965
2014-02-08 Added LM2267 123
2014-02-22 Added ABM8G Crystal
2014-02-25 Added power layout test board
2014-03-08 Added FoxCon 754 socket variant for KAC sensor
2014-03-09 Updated FoxCon socket
2014-03-11 Updated center keepout and handle
2014-03-17 Initial Microzed Top Package
2014-04-09 Added PMOD

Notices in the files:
parts and their libraries:
SparkFun-Connectors: Licensing: CC v3.0 Share-Alike You are welcome to use this library for commercial purposes.
microbuilder: This work is placed in the public domain, and may be freely used for commercial and non-commercial work with the following conditions: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
